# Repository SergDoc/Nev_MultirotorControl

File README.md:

Nev_MultirotorControl
=====================
Baseflight (naze32) port to own STM32F4 board

STM32F407VGT6

MPU6000 on SPI

HMC5883

MS5611

50x50mm 2 layer pcb, 45mm mounting pattern 

8 + 12 PWM I/O  input or output for RC/CPPM/Motors/Servos 

8 channel standard PWM RC input 

PWM (50..1kHz) motor output for up to 12 motors, 8 motors + 4 Servos

Onboard USB connector 

3 UART accessible for telemetry,  firmware update,  Spektrum Satellite RX or GPS

Battery voltage monitoring and low-voltage alarm 

Buzzer for alarm/user notification 

4 Status LEDs

2 VDD & VCC Status LEDs

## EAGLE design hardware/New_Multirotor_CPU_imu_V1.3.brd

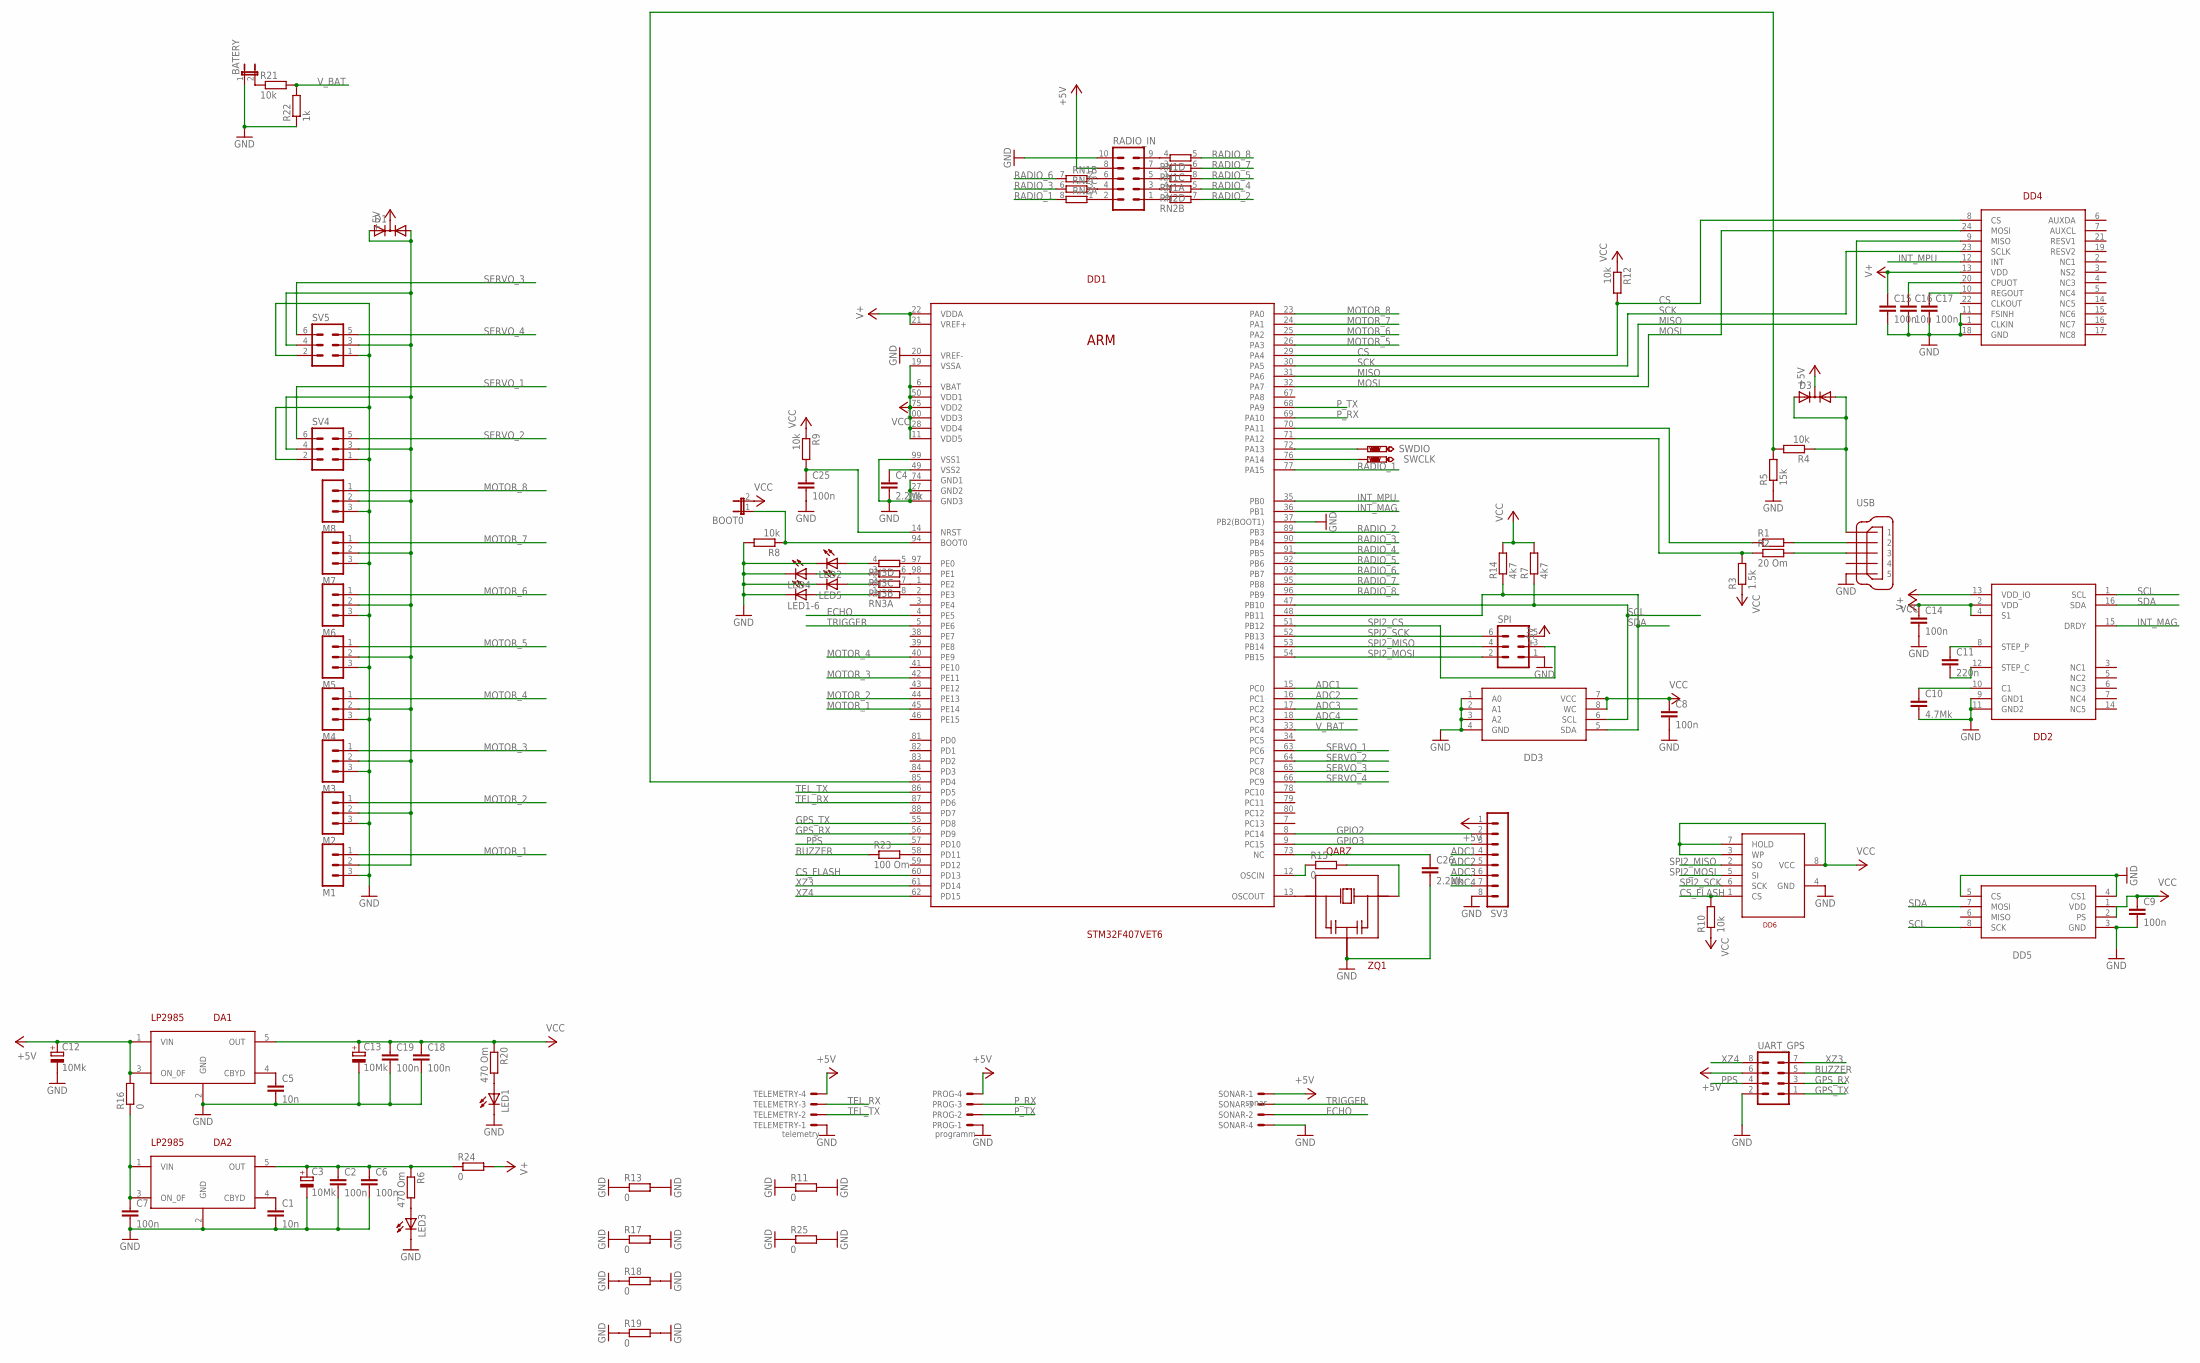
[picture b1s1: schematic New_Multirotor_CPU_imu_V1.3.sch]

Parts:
BATERY: JP1E; JP1
BOOT0: JP1E; JP1
C1, C5, C16: 10n; C0603K
C2, C6, C7, C8, C9, C14, C15, C17, C18, C19, C25: 100n; C0603K
C3, C12, C13: 10Mk; A/3216-18W
C4, C26: 2.2Mk; C0603K
C10: 4.7Mk; C0603K
C11: 220n; C0603K
D1, D3: DIODE-2AC|CASOT23; SOT23
DA1, DA2: LP2985; SOT23-5L
DD1: STM32F407VET6; LQFP100
DD2: HMC5883L; LCC-16
DD3: 24C512; SOIC8
DD4: MPU6000; JEDEC
DD5: MS5611-01BA03
DD6: W25X40; SOIC8
LED1, LED1-6, LED2, LED3, LED4, LED5: LEDCHIPLED_0603; CHIPLED_0603
M1, M2, M3, M4, M5, M6, M7, M8: MA03-1
PROG: programm; SM04B-SRSS-TB
R1: R-EU_R0603; R0603
R2: 20 Om; R0603
R3: 1.5k; R0603
R4, R8, R9, R10, R12, R21: 10k; R0603
R5: 15k; R0603
R6, R20: 470 Om; R0603
R7, R14: 4k7; R0603
R11, R13, R15, R16, R17, R18, R19, R24, R25: 0; R0603
R22: 1k; R0603
R23: 100 Om; R0603
RADIO_IN: MA05-2
RN1, RN2, RN3: 4R-N0603-ARV; 0603-ARV
SONAR: sonar; SM04B-SRSS-TB
SPI: MA03-2
SV3: MA08-1
SV4, SV5: MA03-2
SWCLK: PTR1TP12R; TP12R
SWDIO: PTR1TP12R; TP12R
TELEMETRY: telemetry; SM04B-SRSS-TB
UART_GPS: MA04-2
USB: 32005-201
ZQ1: QARZ

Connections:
+5V: C12.+, D1.3 (C), D3.3 (C), DA1.1 (VIN), DA1.3 (ON_0F), PROG.4, R16.2, RADIO_IN.8, SONAR.1, SPI.5, SV3.1, TELEMETRY.4, UART_GPS.6
ADC1: DD1.15 (PC0), SV3.4
ADC2: DD1.16 (PC1), SV3.5
ADC3: DD1.17 (PC2), SV3.6
ADC4: DD1.18 (PC3), SV3.7
BUZZER: R23.1, UART_GPS.5
CS: DD1.29 (PA4), DD4.8 (CS), R12.2
CS_FLASH: DD1.60 (PD13), DD6.1 (CS), R10.2
ECHO: DD1.4 (PE5), SONAR.2
GND: BATERY.1, C1.2, C2.2, C3.-, C4.2, C5.2, C6.2, C7.2, C8.2, C9.2, C10.2, C12.-, C13.-, C14.2, C15.2, C16.2, C17.2, C18.2, C19.2, C25.2, C26.2, DA1.2 (GND), DA2.2 (GND), DD1.10 (GND3), DD1.20 (VREF-), DD1.27 (GND2), DD1.37 (PB2(BOOT1)), DD1.74 (GND1), DD1.99 (VSS1), DD2.9 (GND1), DD2.11 (GND2), DD3.1 (A0), DD3.2 (A1), DD3.3 (A2), DD3.4 (GND), DD4.1 (CLKIN), DD4.11 (FSINH), DD4.18 (GND), DD5.3 (GND), DD5.4 (CS1), DD5.5 (CS), DD6.4 (GND), LED1.C, LED1-6.C, LED2.C, LED3.C, LED4.C, LED5.C, M1.3, M2.3, M3.3, M4.3, M5.3, M6.3, M7.3, M8.3, PROG.1, R5.1, R8.2, R11.1, R11.2, R13.1, R13.2, R17.1, R17.2, R18.1, R18.2, R19.1, R19.2, R22.1, R25.1, R25.2, RADIO_IN.10, SONAR.4, SPI.1, SV3.8, SV4.1, SV4.2, SV5.1, SV5.2, TELEMETRY.1, UART_GPS.2, USB.5, ZQ1.2
GPIO2: DD1.8 (PC14), SV3.2
GPIO3: DD1.9 (PC15), SV3.3
GPS_RX: DD1.56 (PD9), UART_GPS.3
GPS_TX: DD1.55 (PD8), UART_GPS.1
INT_MAG: DD1.36 (PB1), DD2.15 (DRDY)
INT_MPU: DD1.35 (PB0), DD4.12 (INT)
MISO: DD1.31 (PA6), DD4.9 (MISO)
MOSI: DD1.32 (PA7), DD4.24 (MOSI)
MOTOR_1: DD1.45 (PE14), M1.1
MOTOR_2: DD1.44 (PE13), M2.1
MOTOR_3: DD1.42 (PE11), M3.1
MOTOR_4: DD1.40 (PE9), M4.1
MOTOR_5: DD1.26 (PA3), M5.1
MOTOR_6: DD1.25 (PA2), M6.1
MOTOR_7: DD1.24 (PA1), M7.1
MOTOR_8: DD1.23 (PA0), M8.1
unnamed: DD1.13 (OSCOUT), ZQ1.1
unnamed: R15.2, ZQ1.3
unnamed: DD1.97 (PE0), RN3.5 (2)
unnamed: C1.1, DA2.4 (CBYD)
unnamed: DD1.98 (PE1), RN3.6 (2)
unnamed: LED3.A, R6.2
unnamed: C2.1, C3.+, C6.1, DA2.5 (OUT), R6.1, R24.1
unnamed: RADIO_IN.5, RN1.1
unnamed: C7.1, DA2.1 (VIN), DA2.3 (ON_0F), R16.1
unnamed: DD1.1 (PE2), RN3.7 (2)
unnamed: DD1.2 (PE3), RN3.8 (2)
unnamed: DD1.12 (OSCIN), R15.1
unnamed: LED1.A, R20.2
unnamed: DD1.72 (PA13), SWDIO.TP
unnamed: DD1.76 (PA14), SWCLK.TP
unnamed: LED2.A, RN3.4 (1)
unnamed: LED4.A, RN3.3 (1)
unnamed: C16.1, DD4.20 (CPUOT)
unnamed: D1.1 (A1), D1.2 (A2), M1.2, M2.2, M3.2, M4.2, M5.2, M6.2, M7.2, M8.2, SV4.3, SV4.4, SV5.3, SV5.4
unnamed: RADIO_IN.3, RN2.4 (1)
unnamed: C17.1, DD4.10 (REGOUT)
unnamed: RADIO_IN.9, RN1.4 (1)
unnamed: RADIO_IN.7, RN1.3 (1)
unnamed: BATERY.2, R21.1
unnamed: C10.1, DD2.10 (C1)
unnamed: C11.2, DD2.12 (STEP_C)
unnamed: C11.1, DD2.8 (STEP_P)
unnamed: DD1.58 (PD11), R23.2
unnamed: RADIO_IN.6, RN1.2 (1)
unnamed: RADIO_IN.1, RN2.2 (1)
unnamed: RADIO_IN.4, RN2.3 (1)
unnamed: RADIO_IN.2, RN2.1
unnamed: LED5.A, RN3.2 (1)
unnamed: LED1-6.A, RN3.1
unnamed: DD1.70 (PA11), R1.1
unnamed: DD1.71 (PA12), R2.1, R3.2
unnamed: R1.2, USB.2
unnamed: R2.2, USB.3
unnamed: DD1.85 (PD4), R4.2, R5.2
unnamed: D3.1 (A1), D3.2 (A2), R4.1, USB.1
unnamed: C5.1, DA1.4 (CBYD)
unnamed: C4.1, DD1.49 (VSS2)
unnamed: BOOT0.1, DD1.94 (BOOT0), R8.1
unnamed: C25.1, DD1.14 (NRST), R9.2
unnamed: C26.1, DD1.73 (NC)
PPS: DD1.57 (PD10), UART_GPS.4
P_RX: DD1.69 (PA10), PROG.3
P_TX: DD1.68 (PA9), PROG.2
RADIO_1: DD1.77 (PA15), RN2.8 (2)
RADIO_2: DD1.89 (PB3), RN2.7 (2)
RADIO_3: DD1.90 (PB4), RN2.6 (2)
RADIO_4: DD1.91 (PB5), RN2.5 (2)
RADIO_5: DD1.92 (PB6), RN1.8 (2)
RADIO_6: DD1.93 (PB7), RN1.7 (2)
RADIO_7: DD1.95 (PB8), RN1.6 (2)
RADIO_8: DD1.96 (PB9), RN1.5 (2)
SCK: DD1.30 (PA5), DD4.23 (SCLK)
SCL: DD1.47 (PB10), DD2.1 (SCL), DD3.6 (SCL), DD5.8 (SCK), R7.1
SDA: DD1.48 (PB11), DD2.16 (SDA), DD3.5 (SDA), DD5.7 (MOSI), R14.1
SERVO_1: DD1.63 (PC6), SV4.6
SERVO_2: DD1.64 (PC7), SV4.5
SERVO_3: DD1.65 (PC8), SV5.6
SERVO_4: DD1.66 (PC9), SV5.5
SPI2_CS: DD1.51 (PB12), SPI.3
SPI2_MISO: DD1.53 (PB14), DD6.2 (SO), SPI.4
SPI2_MOSI: DD1.54 (PB15), DD6.5 (SI), SPI.2
SPI2_SCK: DD1.52 (PB13), DD6.6 (SCK), SPI.6
TEL_RX: DD1.87 (PD6), TELEMETRY.3
TEL_TX: DD1.86 (PD5), TELEMETRY.2
TRIGGER: DD1.5 (PE6), SONAR.3
V+: C14.1, C15.1, DD1.21 (VREF+), DD1.22 (VDDA), DD2.2 (VDD), DD2.4 (S1), DD4.13 (VDD), R24.2
VCC: BOOT0.2, C8.1, C9.1, C13.+, C18.1, C19.1, DA1.5 (OUT), DD1.6 (VBAT), DD1.11 (VDD5), DD1.19 (VSSA), DD1.28 (VDD4), DD1.50 (VDD1), DD1.75 (VDD2), DD1.100 (VDD3), DD2.13 (VDD_IO), DD3.7 (VCC), DD3.8 (WC), DD5.1 (VDD), DD5.2 (PS), DD6.3 (WP), DD6.7 (HOLD), DD6.8 (VCC), R3.1, R7.2, R9.1, R10.1, R12.1, R14.2, R20.1
V_BAT: DD1.33 (PC4), R21.2, R22.2
XZ3: DD1.61 (PD14), UART_GPS.7
XZ4: DD1.62 (PD15), UART_GPS.8

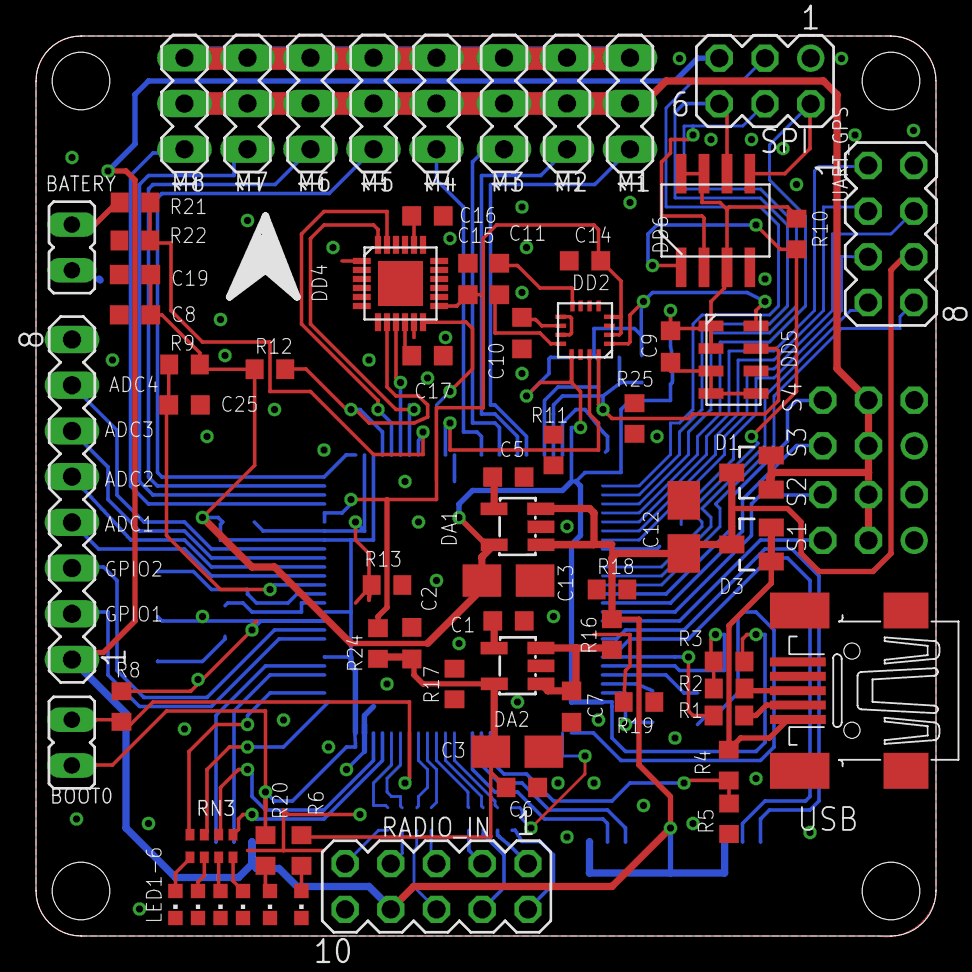
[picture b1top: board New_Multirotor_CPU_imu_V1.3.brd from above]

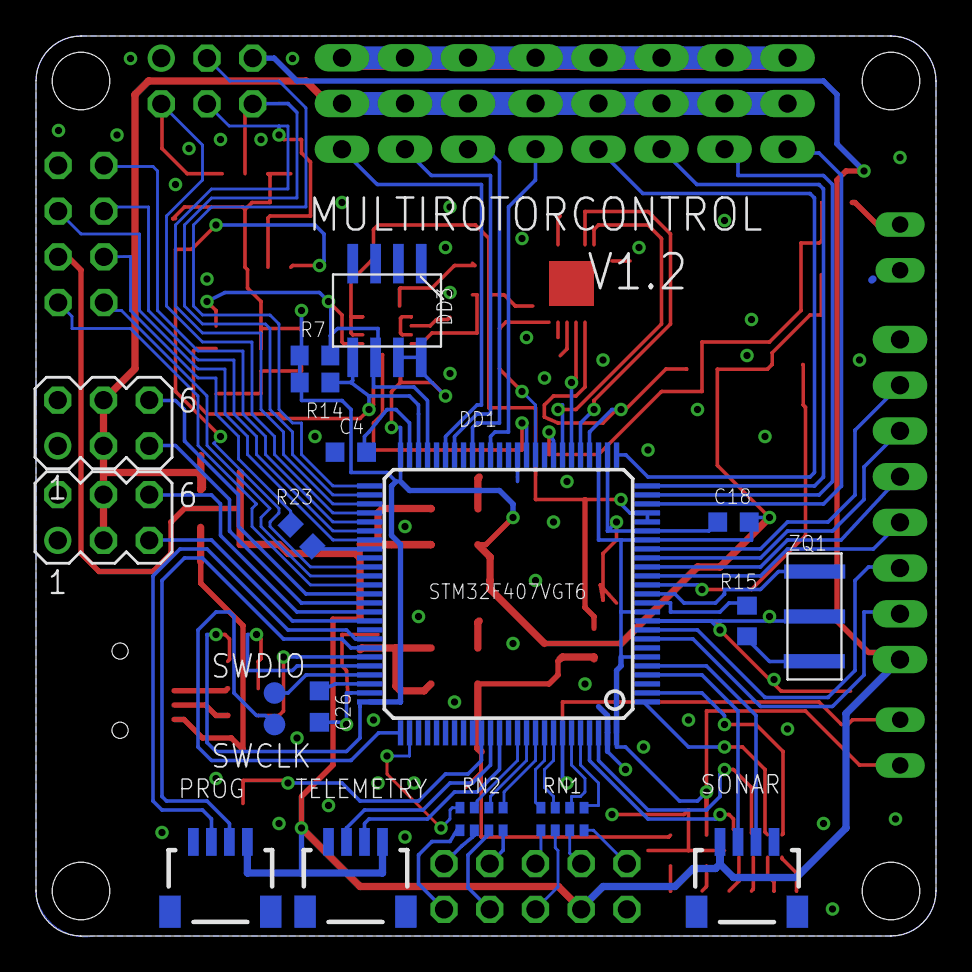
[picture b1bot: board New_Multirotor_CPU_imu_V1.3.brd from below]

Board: 2 copper layers, 50.0 x 50.0 mm, 88 parts (19 on the bottom side), 101 nets.

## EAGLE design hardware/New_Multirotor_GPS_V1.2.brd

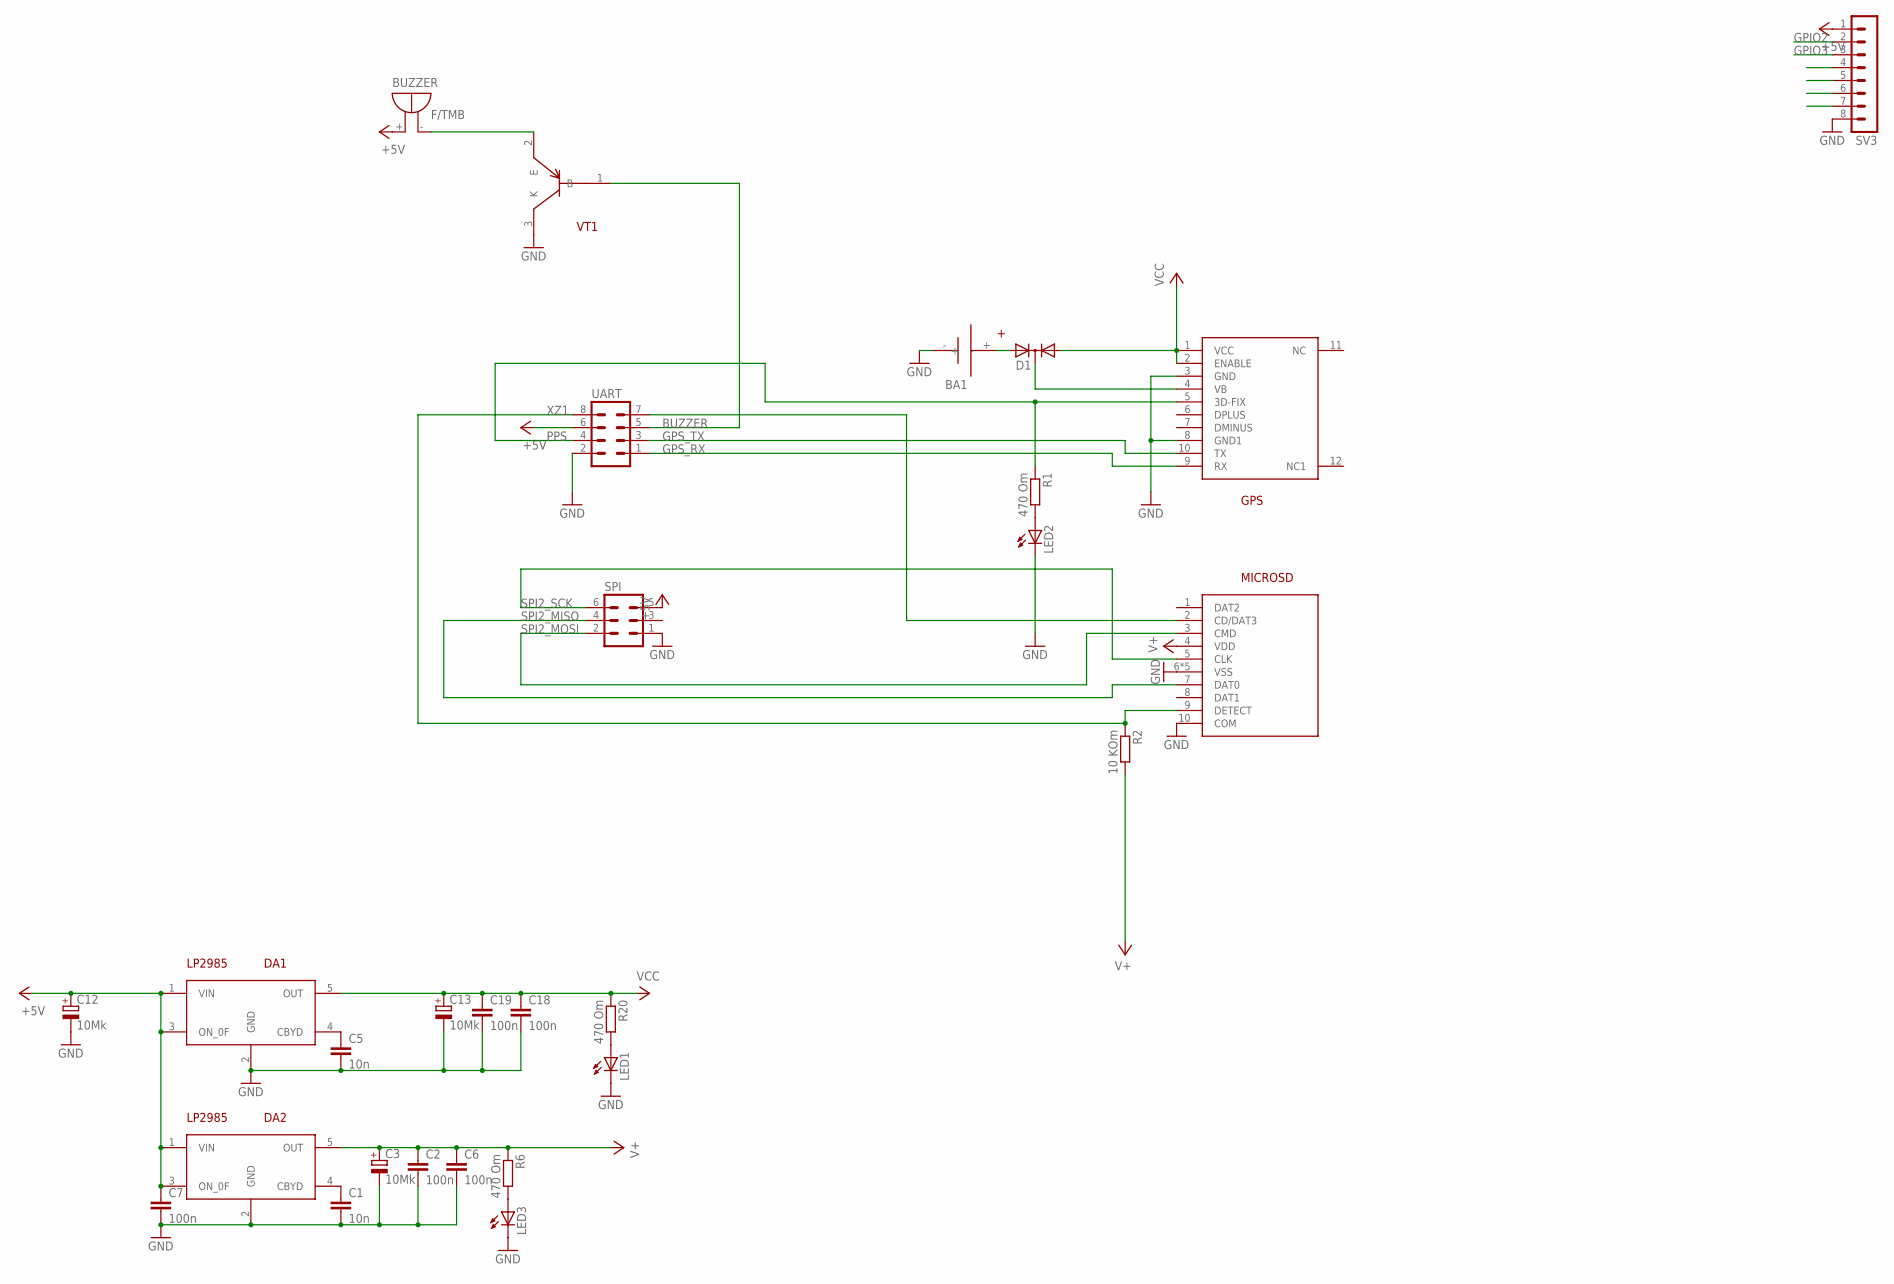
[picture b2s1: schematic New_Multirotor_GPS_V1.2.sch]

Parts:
BA1: BAT
BUZZER: F/TMB
C1, C5: 10n; C0603K
C2, C6, C7, C18, C19: 100n; C0603K
C3, C12, C13: 10Mk; A/3216-18W
D1: DIODE-2AC|CASOT23; SOT23
DA1, DA2: LP2985; SOT23-5L
GPS: FGPMMOPA6B
LED1, LED2, LED3: LEDCHIPLED_0603; CHIPLED_0603
MICROSD: MICROCD_MAIN; MICROSD_MAIN
R1, R6, R20: 470 Om; R0603
R2: 10 KOm; R0603
SPI: MA03-2
SV3: MA08-1
UART: MA04-2
VT1: MMBT3906; SOT23B-3

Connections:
+5V: BUZZER.+, C7.1, C12.+, DA1.1 (VIN), DA1.3 (ON_0F), DA2.1 (VIN), DA2.3 (ON_0F), SPI.5, SV3.1, UART.6
ADC1: SV3.4
ADC2: SV3.5
ADC3: SV3.6
ADC4: SV3.7
BUZZER: UART.5, VT1.1 (B)
GND: BA1.-, C1.2, C2.2, C3.-, C5.2, C6.2, C7.2, C12.-, C13.-, C18.2, C19.2, DA1.2 (GND), DA2.2 (GND), GPS.3 (GND), GPS.8 (GND1), LED1.C, LED2.C, LED3.C, MICROSD.6 (VSS), MICROSD.10 (COM), MICROSD.11 (VSS), MICROSD.12 (VSS), MICROSD.13 (VSS), MICROSD.14 (VSS), SPI.1, SV3.8, UART.2, VT1.3 (K)
GPIO2: SV3.2
GPIO3: SV3.3
GPS_RX: GPS.9 (RX), UART.1
GPS_TX: GPS.10 (TX), UART.3
unnamed: LED2.A, R1.2
unnamed: BUZZER.-, VT1.2 (E)
unnamed: D1.3 (C), GPS.4 (VB)
unnamed: C1.1, DA2.4 (CBYD)
unnamed: BA1.+, D1.2 (A2)
unnamed: LED3.A, R6.2
unnamed: MICROSD.2 (CD/DAT3), UART.7
unnamed: LED1.A, R20.2
unnamed: C5.1, DA1.4 (CBYD)
PPS: GPS.5 (3D-FIX), R1.1, UART.4
SPI2_MISO: MICROSD.7 (DAT0), SPI.4
SPI2_MOSI: MICROSD.3 (CMD), SPI.2
SPI2_SCK: MICROSD.5 (CLK), SPI.6
V+: C2.1, C3.+, C6.1, DA2.5 (OUT), MICROSD.4 (VDD), R2.2, R6.1
VCC: C13.+, C18.1, C19.1, D1.1 (A1), DA1.5 (OUT), GPS.1 (VCC), GPS.2 (ENABLE), R20.1
XZ1: MICROSD.9 (DETECT), R2.1, UART.8

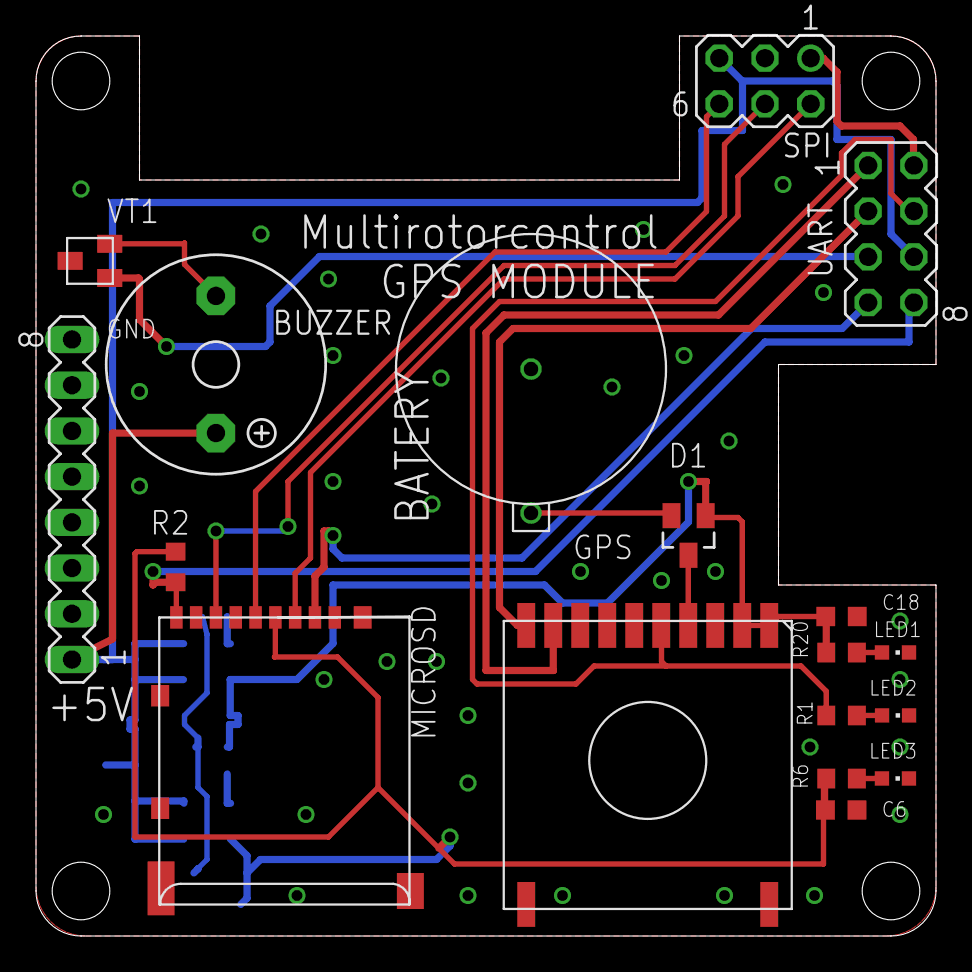
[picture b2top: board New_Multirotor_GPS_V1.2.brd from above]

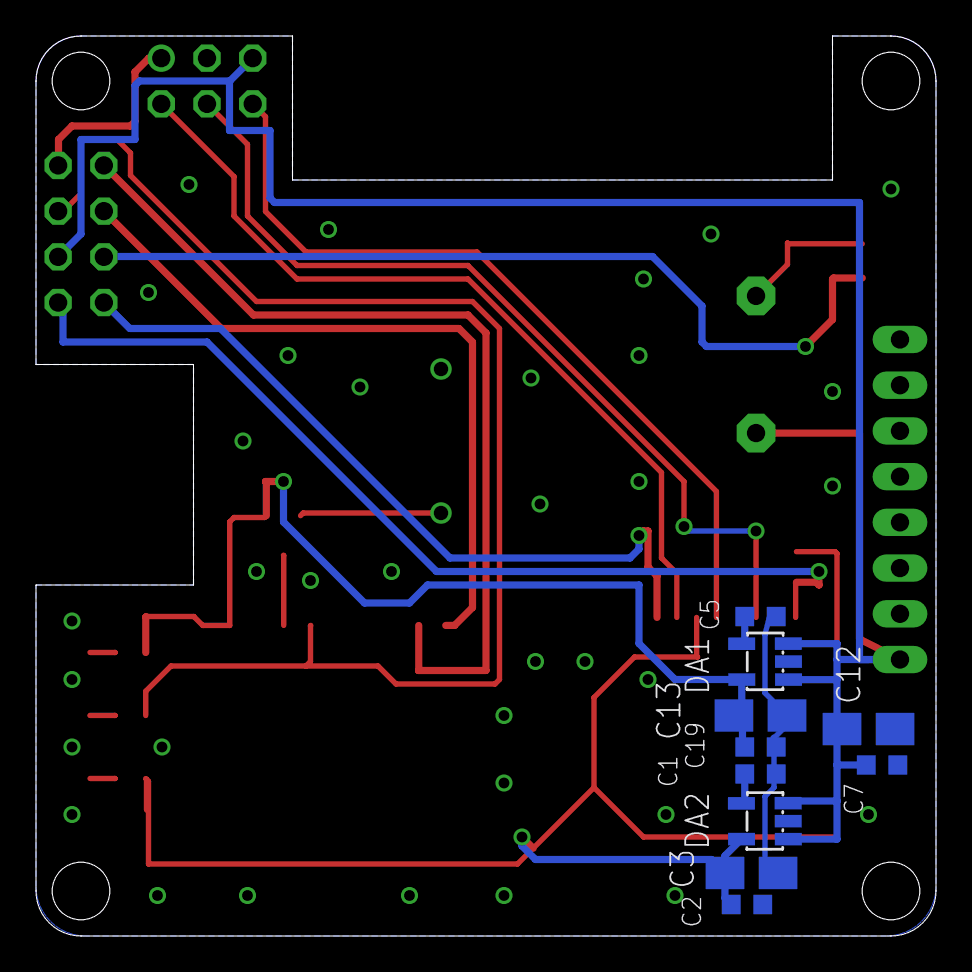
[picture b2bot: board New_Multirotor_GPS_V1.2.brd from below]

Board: 2 copper layers, 50.0 x 50.0 mm, 28 parts (10 on the bottom side), 21 nets.

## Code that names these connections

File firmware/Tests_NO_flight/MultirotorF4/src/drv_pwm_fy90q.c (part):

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
    // Inputs

    // RX1  TIM2_CH1 PA0 [also PPM] [also used for throttle calibration]
    // RX2  TIM2_CH2 PA1
    // RX3  TIM2_CH3 PA2 [also UART2_TX]
    // RX4  TIM2_CH4 PA3 [also UART2_RX]
    // RX5  TIM3_CH1 PA6 [also ADC_IN6]
    // RX6  TIM3_CH2 PA7 [also ADC_IN7]
    // RX7  TIM3_CH3 PB0 [also ADC_IN8]
    // RX8  TIM3_CH4 PB1 [also ADC_IN9]

    // Outputs
    // PWM1 TIM1_CH1 PA8
    // PWM2 TIM1_CH4 PA11
    // PWM3 TIM4_CH1 PB6 [also I2C1_SCL]
    // PWM4 TIM4_CH2 PB7 [also I2C1_SDA]
    // PWM5 TIM4_CH3 PB8
    // PWM6 TIM4_CH4 PB9

    // use PPM or PWM input
    usePPMFlag = init->usePPM;
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
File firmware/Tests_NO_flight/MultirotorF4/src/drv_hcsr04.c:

#include "board.h"
#include "mw.h"

#ifdef SONAR

/* HC-SR04 consists of ultrasonic transmitter, receiver, and control circuits.
 * When trigged it sends out a series of 40KHz ultrasonic pulses and receives
 * echo froman object. The distance between the unit and the object is calculated
 * by measuring the traveling time of sound and output it as the width of a TTL pulse.
 *
 * *** Warning: HC-SR04 operates at +5V ***
 *
 */

static uint16_t trigger_pin;
static uint16_t echo_pin;
static uint32_t exti_line;
static uint8_t exti_pin_source;
static IRQn_Type exti_irqn;

static uint32_t last_measurement;
static volatile int16_t* distance_ptr;

void ECHO_EXTI_IRQHandler(void)
{
    static uint32_t timing_start;
    uint32_t timing_stop;
    if(GPIO_ReadInputDataBit(GPIOB, echo_pin) != 0)
        timing_start = micros();
    else 
    {
        timing_stop = micros();
        if(timing_stop > timing_start) 
        {
            // The speed of sound is 340 m/s or approx. 29 microseconds per centimeter.
            // The ping travels out and back, so to find the distance of the
            // object we take half of the distance traveled.
            //
            // 340 m/s = 0.034 cm/microsecond = 29.41176471 *2 = 58.82352941 rounded to 59
            int32_t pulse_duration = timing_stop - timing_start;          
            *distance_ptr = pulse_duration / 59 ;
        }
    }

    EXTI_ClearITPendingBit(exti_line);   
}

void EXTI1_IRQHandler(void)
{
    ECHO_EXTI_IRQHandler();
}

void EXTI9_5_IRQHandler(void)
{
    ECHO_EXTI_IRQHandler();
}

void hcsr04_init(sonar_config_t config)
{
    GPIO_InitTypeDef GPIO_InitStructure;
    EXTI_InitTypeDef EXTIInit;

    //enable AFIO for EXTI support - already done is drv_system.c
    //RCC_APB2PeriphClockCmd(RCC_APB2Periph_AFIO | RCC_APB2Periph, ENABLE); 

    switch(config)
    {
    case sonar_pwm56:
        trigger_pin = GPIO_Pin_8;   // PWM5 (PB8) - 5v tolerant
        echo_pin = GPIO_Pin_9;      // PWM6 (PB9) - 5v tolerant
        exti_line = EXTI_Line9;
        exti_pin_source = EXTI_PinSource9;
        exti_irqn = EXTI9_5_IRQn;
        break;
    case sonar_rc78:    
        trigger_pin = GPIO_Pin_0;   // RX7 (PB0) - only 3.3v ( add a 1K Ohms resistor )
        echo_pin = GPIO_Pin_1;      // RX8 (PB1) - only 3.3v ( add a 1K Ohms resistor )
        exti_line = EXTI_Line1;
        exti_pin_source = EXTI_PinSource1;
        exti_irqn = EXTI1_IRQn;
        break;
    }
    
    // tp - trigger pin
    //RCC_AHB1PeriphClockCmd(RCC_AHB1Periph_GPIOB, ENABLE);
    GPIO_InitStructure.GPIO_Pin = trigger_pin;
    GPIO_InitStructure.GPIO_Mode = GPIO_Mode_OUT;
    GPIO_InitStructure.GPIO_OType = GPIO_OType_PP;
    GPIO_InitStructure.GPIO_Speed = GPIO_Speed_2MHz;
    GPIO_Init(GPIOB, &GPIO_InitStructure);

    // ep - echo pin
    RCC_AHB1PeriphClockCmd(RCC_AHB1Periph_GPIOB, ENABLE);
    GPIO_InitStructure.GPIO_Pin = echo_pin;
    GPIO_InitStructure.GPIO_Mode = GPIO_Mode_IN;
    GPIO_Init(GPIOB, &GPIO_InitStructure);

    // setup external interrupt on echo pin
    SYSCFG_EXTILineConfig(EXTI_PortSourceGPIOB, exti_pin_source);

    EXTI_ClearITPendingBit(exti_line);
       
    EXTIInit.EXTI_Line = exti_line;
    EXTIInit.EXTI_Mode = EXTI_Mode_Interrupt;
    EXTIInit.EXTI_Trigger = EXTI_Trigger_Rising_Falling;
    EXTIInit.EXTI_LineCmd = ENABLE;    
    EXTI_Init(&EXTIInit);    

    NVIC_EnableIRQ(exti_irqn);

    last_measurement = millis() - 60; // force 1st measurement in hcsr04_get_distance()
}

// distance calculation is done asynchronously, using interrupt
void hcsr04_get_distance(volatile int16_t* distance)
{   
    uint32_t current_time = millis();

    if( current_time < (last_measurement + 60) )
    {
        // the repeat interval of trig signal should be greater than 60ms
        // to avoid interference between connective measurements.
        return;
    }
        
    last_measurement = current_time;
    distance_ptr = distance;

    GPIO_SetBits(GPIOB, trigger_pin);
    //  The width of trig signal must be greater than 10us
    delayMicroseconds(11);
    GPIO_ResetBits(GPIOB, trigger_pin);
}

#endif

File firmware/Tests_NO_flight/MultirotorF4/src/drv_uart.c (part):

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
   
		RCC_AHB1PeriphClockCmd(RCC_AHB1Periph_GPIOA, ENABLE);
		// USART1_TX    PA9
    // USART1_RX    PA10
    GPIO_InitStructure.GPIO_Pin = GPIO_Pin_9;
    GPIO_InitStructure.GPIO_Speed = GPIO_Speed_50MHz;
    GPIO_InitStructure.GPIO_Mode = GPIO_Mode_AF;
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    NVIC_InitStructure.NVIC_IRQChannelCmd = ENABLE;
    NVIC_Init(&NVIC_InitStructure);

    // USART2_TX    PD5
    // USART2_RX    PD6
    GPIO_InitStructure.GPIO_Pin = GPIO_Pin_5;
    GPIO_InitStructure.GPIO_Speed = GPIO_Speed_2MHz;
    GPIO_InitStructure.GPIO_Mode = GPIO_Mode_AF;
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    NVIC_InitStructure.NVIC_IRQChannelCmd = ENABLE;
    NVIC_Init(&NVIC_InitStructure);

    // USART2_TX    PD8
    // USART2_RX    PD9
    GPIO_InitStructure.GPIO_Pin = GPIO_Pin_8;
    GPIO_InitStructure.GPIO_Speed = GPIO_Speed_2MHz;
    GPIO_InitStructure.GPIO_Mode = GPIO_Mode_AF;
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
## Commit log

2012-10-07 new project F4
2013-01-19 hardware add
2013-01-23 Fixes a bug
2013-01-26 Optimized, added the site PA13, PA14 ...
2013-01-27 Перезалил
2013-01-27 Reduced the size to 50x50
2013-01-28 Add Gerbers files
2013-01-30 Add GPS board V1.2
2013-04-02 Add firmware tests NO FLIGHT
2013-04-11 Первые признаки жизни
2013-04-11 fixed led bag
2013-04-19 Fixed a bug with baro
    удалил версию 1.2 добавил 1.3...
2013-04-24 Add pdf
2013-04-28 UART + DMA bag :(
    не работает передача tx :(
2013-06-13 tests Baseflight firmware
    tested firmware afrodevises http://code.google.com/p/afrodevices/
2013-06-22 fix mag
2013-07-07 New PID added
2013-07-16 fix bag PWM
2013-07-20 Release V1
2013-10-14 Fixed bag DMA
2013-10-14 added

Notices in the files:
firmware/Tests_NO_flight/MultirotorF4/src/drv_uart.c:
Copyright © 2011  Bill Nesbitt
